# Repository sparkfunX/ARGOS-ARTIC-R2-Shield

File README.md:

# ARGOS Satellite Transceiver Shield

The [ARGOS ARTIC R2 satellite communication chipset](https://www.cls-telemetry.com/argos-solutions/argos-products/modems/artic-chipset/#1534863095666-398318f3-c367) in Thing Plus format.

[*SparkX ARGOS Satellite Transceiver Shield (SPX-17236)*](https://www.sparkfun.com/products/17236)

_Dimensions are in inches_  

The ARTIC-R2 is an integrated low power small size ARGOS 2/3/4 single chip radio. ARTIC-R2 implements a message based wireless interface. For satellite uplink communication, ARTIC-R2 will encode, modulate and transmit provided user messages. For downlink communication, ARTIC-R2 will lock to the downstream, demodulate and decode it and extract the satellite messages.

The ARTIC-R2 can transmit signals in frequency bands around 400MHz and receive signals in the bands around 466MHz, in accordance with the ARGOS satellite system specifications. The ARTIC-R2 is compliant to all ARGOS 3 and ARGOS 4 RX and TX standards. It contains a RF transceiver and frequency synthesizer and a digital baseband modem. The ARTIC-R2 contains an on-chip power amplifier delivering 1mW [0dBm] output power, that serves as an output for connecting an external high efficient PA. The (de)modulation algorithms run on an on-chip DSP. This software approach allows for retargeting the ARTIC for other applications. The DSP program can be retained on an external flash or the MCU.

- Serial interface (SPI) for communication with MCU
- Programmable DSP core on board to ensure flexibility
- RX frequency : 466MHz – TX frequency: 400MHz
- Fractional N frequency synthesis
- Supported TX standards:
  - BPSK: PTT-A2 (ARGOS 2), PTT-VLD (ARGOS 4)
  - QPSK: PTT-A3, PTT-ZE (ARGOS 3)
  - GMSK: PTT-HD (ARGOS 3), PTT-MD (ARGOS 4), PTT-HD (ARGOS 4)
- Supported RX standards:
  - BPSK: PMT-A3 (ARGOS 3)
  - DSSS OQPSK: PMT-A4 (ARGOS 4) not available
- Dedicated flash Interface to retain Firmware
- Support COSPAS-SARSAT standard
- Operates on external 26MHz reference clock
- Dual supply, 1.8V and 3.3V
- Integrated PA (0dBm) to combine with external PA

An RFPA0133 programmable gain power amplifier boosts the 0dBm (1mW) output from the ARTIC by up to 26dB, producing a maximum transmit power level of 400mW. The transmit power can be adjusted via the **G8** breakout pin.

The ARGOS satellite system is **currently** restricted to specific programs and applications. Please check that your project meets these requirements before buying hardware. [CLS (France)](https://www.cls-telemetry.com/argos-solutions/) and the [Woods Hole Group (America)](https://www.clsamerica.com/science-with-argos) will be able to advise if your project meets the requirements.
- _**"To meet system use requirements, all programs using Argos have to be related in some way or other to environmental protection, awareness or study, or to protecting human life."**_

## Repository Contents

- [**/Documents**](./Documents) - Datasheets, test certificates etc.
- [**/Hardware**](./Hardware) - Eagle PCB, SCH and LBR design files
- [**LICENSE.md**](./LICENSE,md) - contains the licence information

## Documentation

- [**Arduino Library**](https://github.com/sparkfun/SparkFun_ARGOS_ARTIC_R2_Arduino_Library) - SparkFun ARGOS ARTIC R2 Arduino Library
- [**Hookup Guide**](https://learn.sparkfun.com/tutorials/argos-artic-r2-satellite-transceiver-shield-hookup-guide) - a hookup guide for the SparkFun ARGOS Satellite Transceiver Shield - ARTIC R2

## Thanks

The SparkX ARGOS Satellite Transceiver Shield is a remix of the reference design kindly provided by the Arribada Initiative and Icoteq Ltd.

## License Information

This product is _**open source**_! 

Please review the LICENSE.md file for license information. 

If you have any questions or concerns on licensing, please contact technical support on our [SparkFun forums](https://forum.sparkfun.com/viewforum.php?f=152).

Distributed as-is; no warranty is given.

- Your friends at SparkFun.

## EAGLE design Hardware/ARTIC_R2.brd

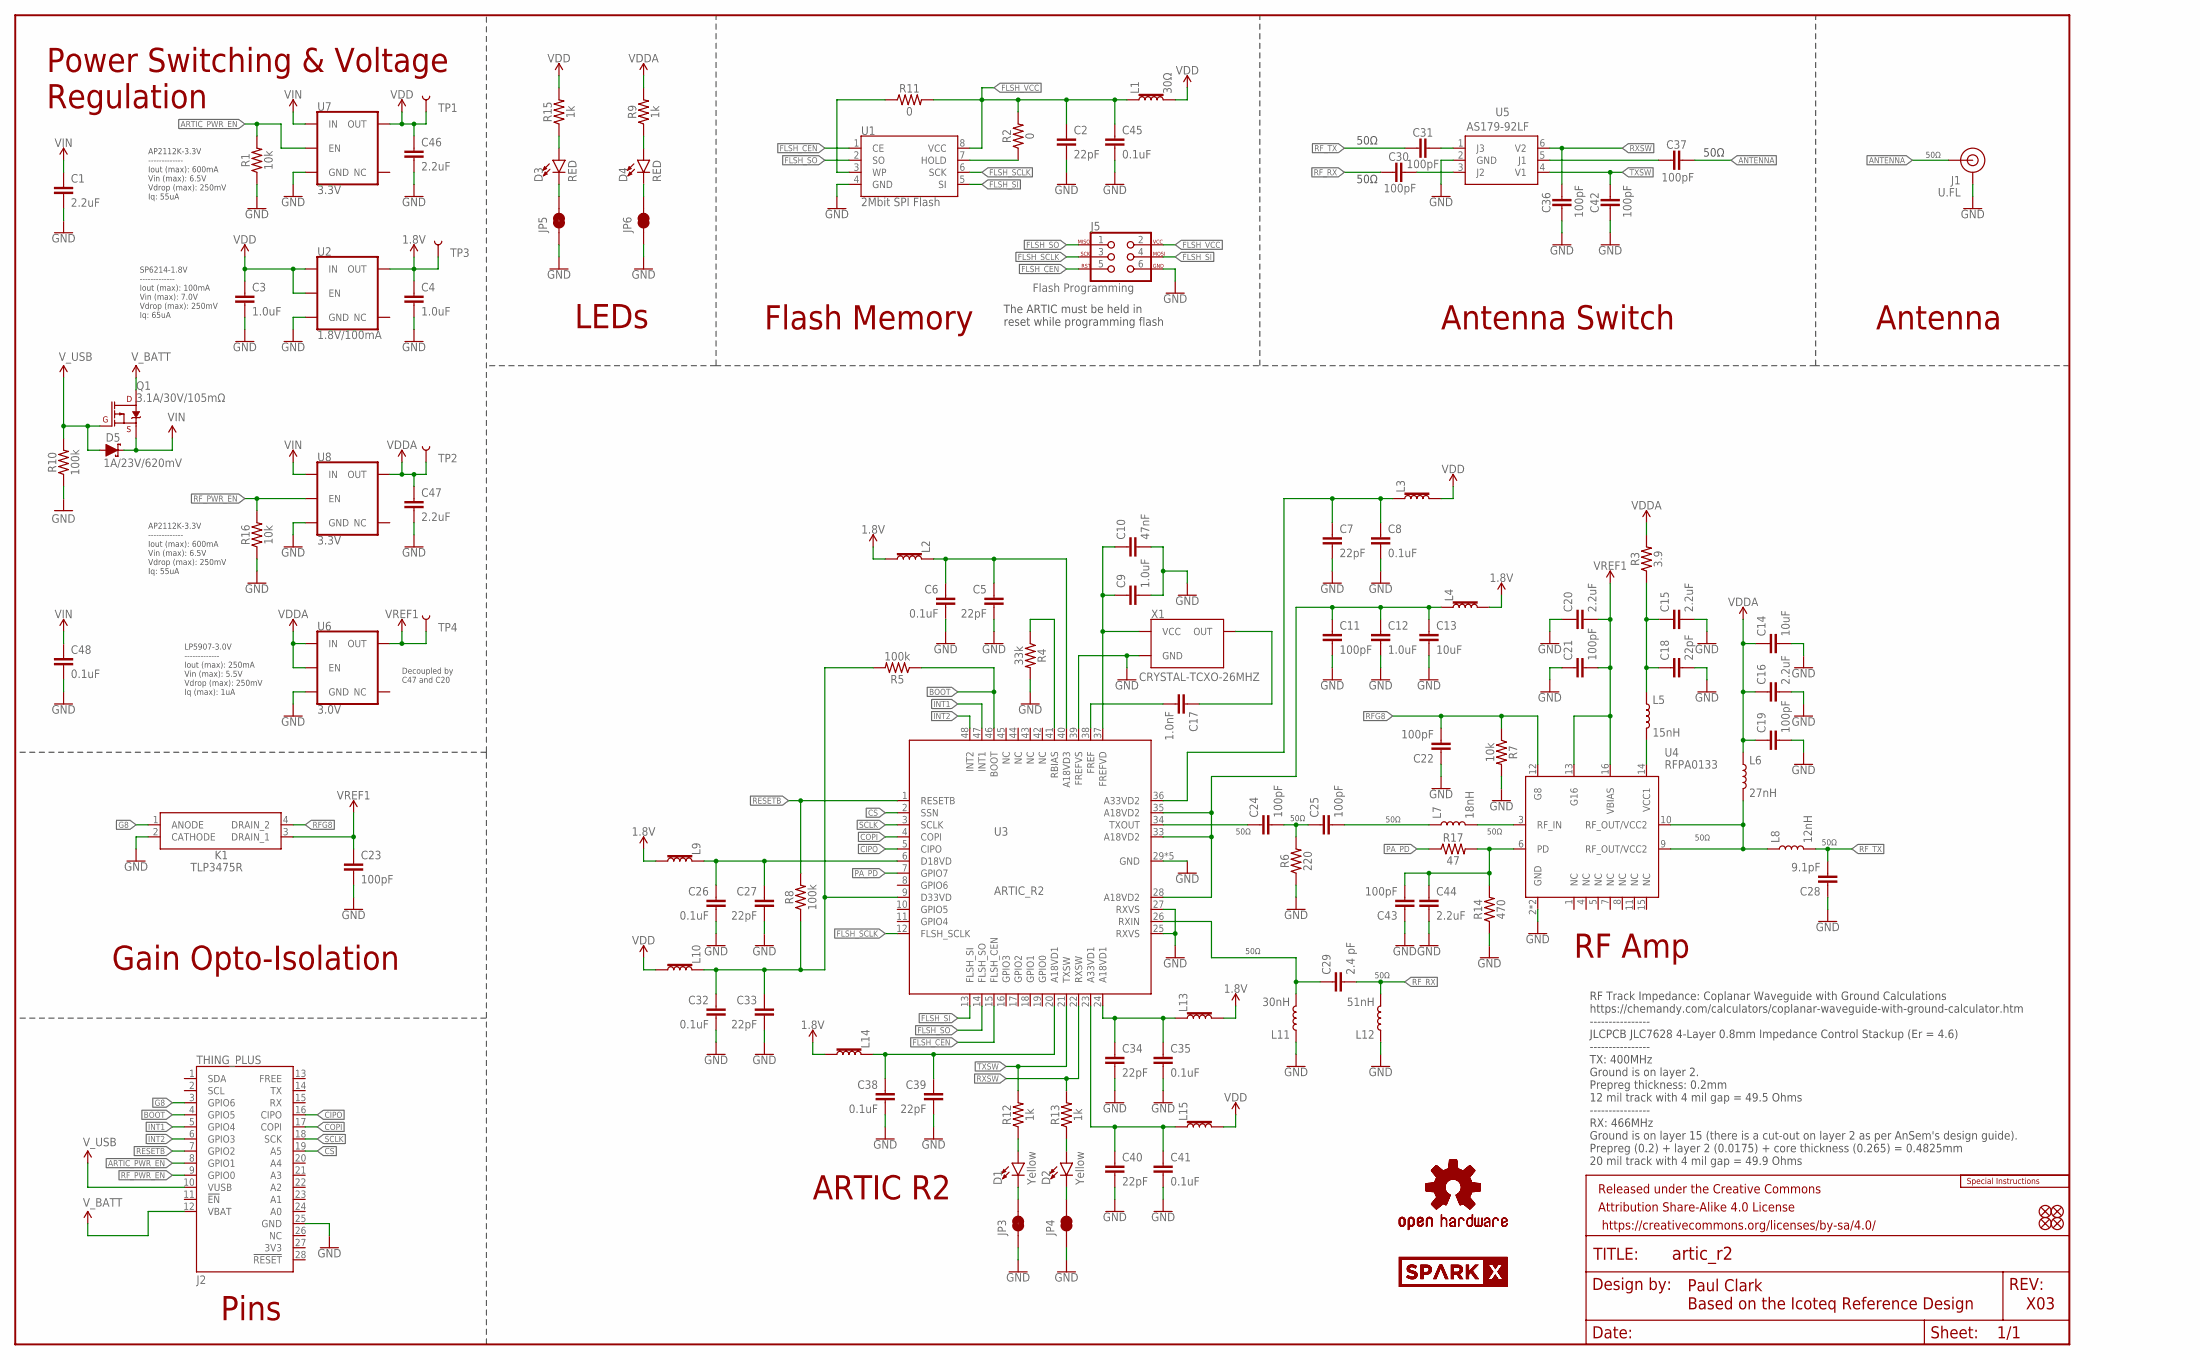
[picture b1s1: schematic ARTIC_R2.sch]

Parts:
C1, C15, C16, C20, C44, C46, C47: 2.2uF; 0402-TIGHT
C2, C5, C7, C18, C27, C33, C34, C39, C40: 22pF; 0402-TIGHT
C3, C4, C9, C12: 1.0uF; 0402-TIGHT
C6, C8, C26, C32, C35, C38, C41, C45, C48: 0.1uF; 0402-TIGHT
C10: 47nF; 0402-TIGHT
C11, C19, C21, C22, C23, C24, C25, C30, C31, C36, C37, C42, C43: 100pF; 0402-TIGHT
C13, C14: 10uF; 0402-TIGHT
C17: 1.0nF; 0402-TIGHT
C28: 9.1pF; 0402-TIGHT
C29: 2.4 pF; 0402_MURATA
D1, D2: Yellow; LED-0603
D3, D4: RED; LED-0603
D5: 1A/23V/620mV; SOD-323
FD1, FD2, FD3, FD4: FIDUCIAL1X2; FIDUCIAL-1X2
FRAME1: FRAME-LEDGER; CREATIVE_COMMONS
J1: U.FL
J2: THING_PLUS
J5: Flash Programming; 2X3_TEST_POINTS
JP3, JP4, JP5, JP6: JUMPER-SMT_2_NC_TRACE_SILK; SMT-JUMPER_2_NC_TRACE_SILK
K1: TLP3475R; TLP3475RTPF
L1, L2, L3, L4, L9, L10, L13, L14, L15: 30Ω; 0402-TIGHT
L5: 15nH; 0402_COILCRAFT
L6: 27nH; 0402_COILCRAFT
L7: 18nH; 0402_COILCRAFT
L8: 12nH; 0402_COILCRAFT
L11: 30nH; 0402_COILCRAFT
L12: 51nH; 0402_COILCRAFT
LOGO1: SPECIAL_INSTRUCTIONS-ORDERING; ORDERING_INSTRUCTIONS
LOGO2, LOGO3: OSHW-LOGOS; OSHW-LOGO-S
Q1: 3.1A/30V/105mΩ; SOT23-3
R1, R7, R16: 10k; 0402-TIGHT
R2, R11: 0; 0402-TIGHT
R3: 3.9; 0402-TIGHT
R4: 33k; 0402-TIGHT
R5, R8, R10: 100k; 0402-TIGHT
R6: 220; 0402-TIGHT
R9, R12, R13, R15: 1k; 0402-TIGHT
R14: 470; 0402-TIGHT
R17: 47; 0402-TIGHT
SPARKX1, SPARKX2: SPARKX-LOGO4; SPARKX-MEDIUM
TP1, TP2, TP3, TP4: TEST-POINTTP_15TH_THRU; TP_15TH
U1: 2Mbit SPI Flash; SO08
U2: 1.8V/100mA; SC70
U3: ARTIC_R2; QFN-48
U4: RFPA0133; QFN50P300X300X86-17N
U5: AS179-92LF; SOT65P220X100-6N
U6: 3.0V; SOT23-5
U7, U8: 3.3V; SOT23-5
X1: CRYSTAL-TCXO-26MHZ; CRYSTAL-TCXO-SMD-1.65X1.25

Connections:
1.8V: C4.1, L2.2, L4.2, L9.2, L13.2, L14.2, TP3.P$1, U2.5 (OUT)
ANTENNA: C37.1, J1.FEED (SIGNAL)
ARTIC_PWR_EN: J2.8 (GPIO1), R1.2, U7.3 (EN)
BOOT: J2.4 (GPIO5), R5.1, U3.46 (BOOT)
CIPO: J2.16 (CIPO), U3.5 (CIPO)
COPI: J2.17 (COPI), U3.4 (COPI)
CS: J2.19 (A5), U3.2 (SSN)
FLSH_CEN: J5.5, U1.1 (CE), U3.15 (FLSH_CEN)
FLSH_SCLK: J5.3, U1.6 (SCK), U3.12 (FLSH_SCLK)
FLSH_SI: J5.4, U1.5 (SI), U3.13 (FLSH_SI)
FLSH_SO: J5.1, U1.2 (SO), U3.14 (FLSH_SO)
FLSH_VCC: C2.1, C45.1, J5.2, L1.1, R2.2, R11.2, U1.8 (VCC)
G8: J2.3 (GPIO6), K1.1 (ANODE)
GND: C1.2, C2.2, C3.2, C4.2, C5.2, C6.2, C7.2, C8.2, C9.2, C10.2, C11.2, C12.2, C13.2, C14.2, C15.2, C16.2, C18.2, C19.2, C20.1, C21.1, C22.1, C23.2, C26.2, C27.2, C28.1, C32.2, C33.2, C34.2, C35.2, C36.2, C38.2, C39.2, C40.2, C41.2, C42.2, C43.1, C44.2, C45.2, C46.2, C47.2, C48.2, J1.1 (GND), J1.2 (GND), J2.25 (GND), J5.6, JP3.1, JP4.1, JP5.1, JP6.1, K1.2 (CATHODE), L11.P$1 (1), L12.P$1 (1), R1.1, R4.2, R6.1, R7.2, R10.1, R14.1, R16.1, U1.4 (GND), U2.2 (GND), U3.25 (RXVS), U3.27 (RXVS), U3.29 (GND), U3.30 (GND), U3.31 (GND), U3.32 (GND), U3.39 (FREFVS), U3.GND, U4.2 (GND), U4.EDAP (GND), U5.2 (GND), U6.2 (GND), U7.2 (GND), U8.2 (GND), X1.1 (GND), X1.2 (GND)
INT1: J2.5 (GPIO4), U3.47 (INT1)
INT2: J2.6 (GPIO3), U3.48 (INT2)
unnamed: R2.1, U1.7 (HOLD)
unnamed: R11.1, U1.3 (WP)
unnamed: C34.1, C35.1, L13.1, U3.24 (A18VD1)
unnamed: C40.1, C41.1, L15.1, U3.23 (A33VD1)
unnamed: D2.A, R13.1
unnamed: D1.A, R12.1
unnamed: C26.1, C27.1, L9.1, U3.6 (D18VD)
unnamed: C32.1, C33.1, L10.1, R5.2, R8.1, U3.9 (D33VD)
unnamed: C11.1, C12.1, C13.1, L4.1, U3.28 (A18VD2), U3.33 (A18VD2), U3.35 (A18VD2)
unnamed: C7.1, C8.1, L3.1, U3.36 (A33VD2)
unnamed: R4.1, U3.41 (RBIAS)
unnamed: C5.1, C6.1, L2.1, U3.40 (A18VD3)
unnamed: C9.1, C10.1, U3.37 (FREFVD), X1.4 (VCC)
unnamed: C17.1, X1.3 (OUT)
unnamed: C17.2, U3.38 (FREF)
unnamed: C24.1, U3.34 (TXOUT)
unnamed: C24.2, C25.1, R6.2
unnamed: L5.P$2 (2), U4.14 (VCC1)
unnamed: C15.1, C18.1, L5.P$1 (1), R3.1
unnamed: C29.P$1 (1), L11.P$2 (2), U3.26 (RXIN)
unnamed: D4.A, R9.1
unnamed: C25.2, L7.P$1 (1)
unnamed: L7.P$2 (2), U4.3 (RF_IN)
unnamed: L6.P$2 (2), L8.P$1 (1), U4.9 (RF_OUT/VCC2), U4.10 (RF_OUT/VCC2)
unnamed: D4.C, JP6.2
unnamed: C31.1, U5.1 (J3)
unnamed: C30.1, U5.3 (J2)
unnamed: C37.2, U5.5 (J1)
unnamed: C38.1, C39.1, L14.1, U3.20 (A18VD1)
unnamed: D1.C, JP3.2
unnamed: D2.C, JP4.2
unnamed: D3.A, R15.1
unnamed: D3.C, JP5.2
PA_PD: R17.1, U3.7 (GPIO7)
PD: C43.2, C44.1, R14.2, R17.2, U4.6 (PD)
RESETB: J2.7 (GPIO2), R8.2, U3.1 (RESETB)
RFG8: C22.2, K1.4 (DRAIN_2), R7.1, U4.12 (G8)
RF_PWR_EN: J2.9 (GPIO0), R16.2, U8.3 (EN)
RF_RX: C29.P$2 (2), C30.2, L12.P$2 (2)
RF_TX: C28.2, C31.2, L8.P$2 (2)
RXSW: C36.1, R13.2, U3.22 (RXSW), U5.6 (V2)
SCLK: J2.18 (SCK), U3.3 (SCLK)
TXSW: C42.1, R12.2, U3.21 (TXSW), U5.4 (V1)
VDD: C3.1, C46.1, L1.2, L3.2, L10.2, L15.2, R15.2, TP1.P$1, U2.1 (IN), U2.3 (EN), U7.5 (OUT)
VDDA: C14.1, C16.1, C19.1, C47.1, L6.P$1 (1), R3.2, R9.2, TP2.P$1, U6.1 (IN), U6.3 (EN), U8.5 (OUT)
VIN: C1.1, C48.1, D5.C, Q1.2 (S), U7.1 (IN), U8.1 (IN)
VREF1: C20.2, C21.2, C23.1, K1.3 (DRAIN_1), TP4.P$1, U4.13 (G16), U4.16 (VBIAS), U6.5 (OUT)
V_BATT: J2.12 (VBAT), Q1.3 (D)
V_USB: D5.A, J2.10 (VUSB), Q1.1 (G), R10.2

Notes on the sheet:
Paul Clark Based on the Icoteq Reference Design
X03
SP6214-1.8V ------------- Iout (max): 100mA Vin (max): 7.0V Vdrop (max): 250mV Iq: 65uA
Power Switching & Voltage Regulation
Flash Memory
Antenna Switch
Antenna
ARTIC R2
RF Amp
Pins
50Ω
LEDs
RF Track Impedance: Coplanar Waveguide with Ground Calculations https://chemandy.com/calculators/coplanar-waveguide-with-ground-calculator.htm ---------------- JLCPCB JLC7628 4-Layer 0.8mm Impedance Control Stackup (Er = 4.6) ---------------- TX: 400MHz Ground is on layer 2. Prepreg thickness: 0.2m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
Gain Opto-Isolation
The ARTIC must be held in reset while programming flash
AP2112K-3.3V ------------- Iout (max): 600mA Vin (max): 6.5V Vdrop (max): 250mV Iq: 55uA
LP5907-3.0V ------------- Iout (max): 250mA Vin (max): 5.5V Vdrop (max): 250mV Iq (max): 1uA
Decoupled by C47 and C20

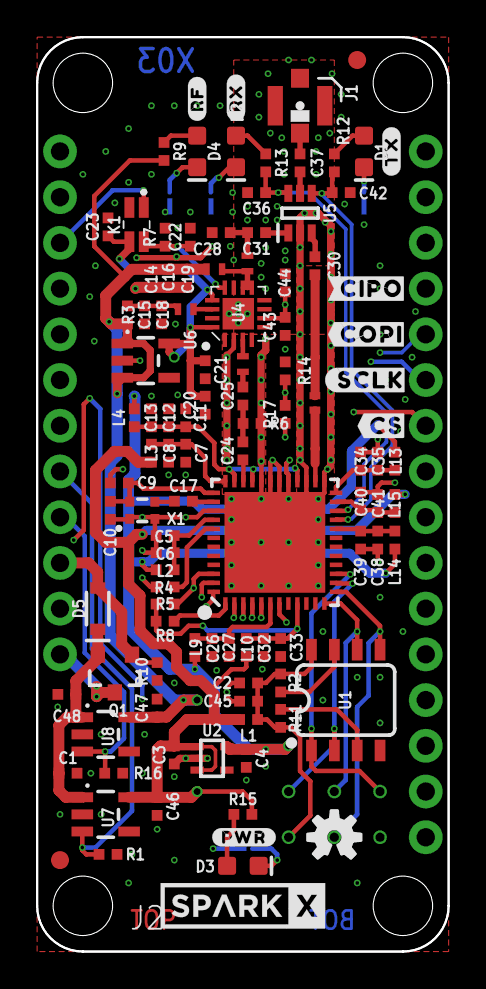
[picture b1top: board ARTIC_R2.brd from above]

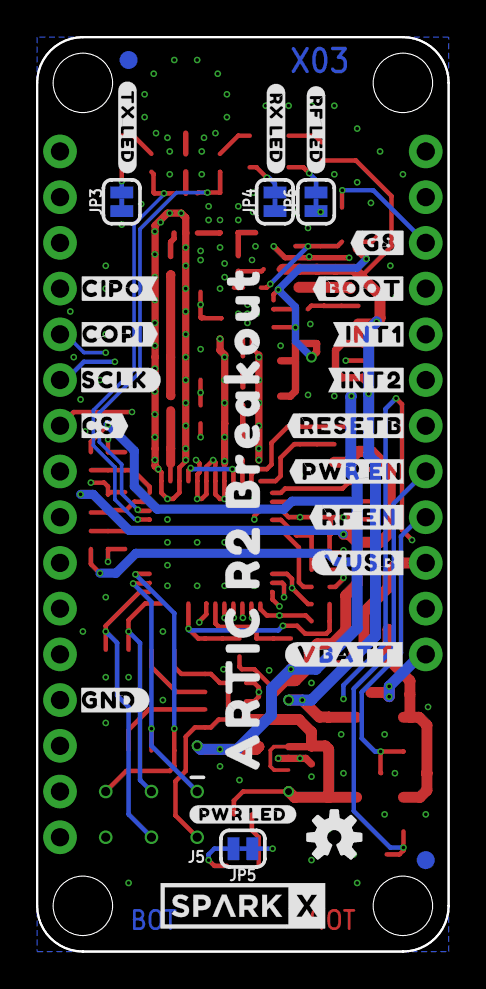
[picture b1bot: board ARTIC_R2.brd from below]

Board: 4 copper layers, 22.9 x 50.8 mm, 144 parts (28 on the bottom side), 65 nets.

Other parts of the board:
U$1: #TX#0
U$2: #RX#0
U$3: #RX_LED#0
U$4: #TX_LED#0
U$5: #RF_LED#0
U$6: #G8#0
U$7: #RF#0
U$8: #RF_EN#0
U$9: CIPO#0
U$10: #CIPO0
U$11: #COPI0
U$12: COPI#0
U$13: #SCLK0
U$14: SCLK#0
U$15: #CS0
U$16: CS#0
U$17: GND#0
U$18: #RESETB0
U$19: #PWR_EN0
U$20: #VBATT#0
U$21: #VUSB#0
U$24: #BOOT0
U$25: #INT10
U$26: #INT20
U$27: #PWR_LED#0
U$28: #PWR#0
U$29: ARTIC_R2_BREAKOUT0

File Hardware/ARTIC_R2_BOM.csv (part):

Part,Value,Device,Package,Description,DESCRIPTION,DESIGNER,DIGIKEY_PART,MANUFACTURER,MANUFACTURER_NAME,MANUFACTURER_PART_NUMBER,MANU_PART,MOUSER_PART,MOUSER_PART_NUMBER,MOUSER_PRICE-STOCK,PACKAGE,PROD_ID,REV,SF_ID,VALUE
C1,2.2uF,2.2UF-0402_TIGHT-10V-10%-X5R,0402-TIGHT,2.2µF ceramic capacitors,,,,,,,,,,,,CAP-14232,,,2.2uF
C2,22pF,22PF-0402T-16V-10%,0402-TIGHT,22pF ceramic capacitors,,,,,,,,,,,,CAP-14674,,,22pF
C3,1.0uF,1.0UF-0402T-16V-10%,0402-TIGHT,1µF ceramic capacitors,,,,,,,,,,,,CAP-12417,,,1.0uF
C4,1.0uF,1.0UF-0402T-16V-10%,0402-TIGHT,1µF ceramic capacitors,,,,,,,,,,,,CAP-12417,,,1.0uF
C5,22pF,22PF-0402T-16V-10%,0402-TIGHT,22pF ceramic capacitors,,,,,,,,,,,,CAP-14674,,,22pF
C6,0.1uF,0.1UF-0402T-6.3V-10%-X7R,0402-TIGHT,0.1µF ceramic capacitors,,,,,,,,,,,,CAP-14993,,,0.1uF
C7,22pF,22PF-0402T-16V-10%,0402-TIGHT,22pF ceramic capacitors,,,,,,,,,,,,CAP-14674,,,22pF
C8,0.1uF,0.1UF-0402T-6.3V-10%-X7R,0402-TIGHT,0.1µF ceramic capacitors,,,,,,,,,,,,CAP-14993,,,0.1uF
C9,1.0uF,1.0UF-0402T-16V-10%,0402-TIGHT,1µF ceramic capacitors,,,,,,,,,,,,CAP-12417,,,1.0uF
C10,47nF,47NF-0402_TIGHT-25V-10%-X7R,0402-TIGHT,47nF ceramic capacitors,,,,,,,,,,,,CAP-14243,,,47nF
C11,100pF,100PF-0402T-50V-5%,0402-TIGHT,100pF/0.1nF ceramic capacitors,,,,,,,,,,,,CAP-13458,,,100pF
C12,1.0uF,1.0UF-0402T-16V-10%,0402-TIGHT,1µF ceramic capacitors,,,,,,,,,,,,CAP-12417,,,1.0uF
C13,10uF,10UF-0402T-6.3V-20%,0402-TIGHT,10.0µF ceramic capacitors,,,,,,,,,,,,CAP-14848,,,10uF
C14,10uF,10UF-0402T-6.3V-20%,0402-TIGHT,10.0µF ceramic capacitors,,,,,,,,,,,,CAP-14848,,,10uF
C15,2.2uF,2.2UF-0402_TIGHT-10V-10%-X5R,0402-TIGHT,2.2µF ceramic capacitors,,,,,,,,,,,,CAP-14232,,,2.2uF
C16,2.2uF,2.2UF-0402_TIGHT-10V-10%-X5R,0402-TIGHT,2.2µF ceramic capacitors,,,,,,,,,,,,CAP-14232,,,2.2uF
C17,1.0nF,1.0NF/1000PF-0402_TIGHT-50V-10%,0402-TIGHT,"1nF/1,000pF ceramic capacitors",,,,,,,,,,,,CAP-14280,,,1.0nF
C18,22pF,22PF-0402T-16V-10%,0402-TIGHT,22pF ceramic capacitors,,,,,,,,,,,,CAP-14674,,,22pF
C19,100pF,100PF-0402T-50V-5%,0402-TIGHT,100pF/0.1nF ceramic capacitors,,,,,,,,,,,,CAP-13458,,,100pF
C20,2.2uF,2.2UF-0402_TIGHT-10V-10%-X5R,0402-TIGHT,2.2µF ceramic capacitors,,,,,,,,,,,,CAP-14232,,,2.2uF
C21,100pF,100PF-0402T-50V-5%,0402-TIGHT,100pF/0.1nF ceramic capacitors,,,,,,,,,,,,CAP-13458,,,100pF
C22,100pF,100PF-0402T-50V-5%,0402-TIGHT,100pF/0.1nF ceramic capacitors,,,,,,,,,,,,CAP-13458,,,100pF
C23,100pF,100PF-0402T-50V-5%,0402-TIGHT,100pF/0.1nF ceramic capacitors,,,,,,,,,,,,CAP-13458,,,100pF
C24,100pF,100PF-0402T-50V-5%,0402-TIGHT,100pF/0.1nF ceramic capacitors,,,,,,,,,,,,CAP-13458,,,100pF
C25,100pF,100PF-0402T-50V-5%,0402-TIGHT,100pF/0.1nF ceramic capacitors,,,,,,,,,,,,CAP-13458,,,100pF
C26,0.1uF,0.1UF-0402T-6.3V-10%-X7R,0402-TIGHT,0.1µF ceramic capacitors,,,,,,,,,,,,CAP-14993,,,0.1uF
C27,22pF,22PF-0402T-16V-10%,0402-TIGHT,22pF ceramic capacitors,,,,,,,,,,,,CAP-14674,,,22pF
C28,9.1pF,9.1PF-0402-TIGHT,0402-TIGHT,9.1pF ceramic capacitors,,,,,,,,609-500R07S9R1CV4T,,,,CAP-15278,,,9.1pF
C29,2.4 pF,2.4PF-0402,0402_MURATA,,,,,,,,,,,,,CAP-14351,,,2.4 pF
C30,100pF,100PF-0402T-50V-5%,0402-TIGHT,100pF/0.1nF ceramic capacitors,,,,,,,,,,,,CAP-13458,,,100pF
C31,100pF,100PF-0402T-50V-5%,0402-TIGHT,100pF/0.1nF ceramic capacitors,,,,,,,,,,,,CAP-13458,,,100pF
C32,0.1uF,0.1UF-0402T-6.3V-10%-X7R,0402-TIGHT,0.1µF ceramic capacitors,,,,,,,,,,,,CAP-14993,,,0.1uF
C33,22pF,22PF-0402T-16V-10%,0402-TIGHT,22pF ceramic capacitors,,,,,,,,,,,,CAP-14674,,,22pF
C34,22pF,22PF-0402T-16V-10%,0402-TIGHT,22pF ceramic capacitors,,,,,,,,,,,,CAP-14674,,,22pF
C35,0.1uF,0.1UF-0402T-6.3V-10%-X7R,0402-TIGHT,0.1µF ceramic capacitors,,,,,,,,,,,,CAP-14993,,,0.1uF
C36,100pF,100PF-0402T-50V-5%,0402-TIGHT,100pF/0.1nF ceramic capacitors,,,,,,,,,,,,CAP-13458,,,100pF
C37,100pF,100PF-0402T-50V-5%,0402-TIGHT,100pF/0.1nF ceramic capacitors,,,,,,,,,,,,CAP-13458,,,100pF
C38,0.1uF,0.1UF-0402T-6.3V-10%-X7R,0402-TIGHT,0.1µF ceramic capacitors,,,,,,,,,,,,CAP-14993,,,0.1uF
C39,22pF,22PF-0402T-16V-10%,0402-TIGHT,22pF ceramic capacitors,,,,,,,,,,,,CAP-14674,,,22pF
C40,22pF,22PF-0402T-16V-10%,0402-TIGHT,22pF ceramic capacitors,,,,,,,,,,,,CAP-14674,,,22pF
C41,0.1uF,0.1UF-0402T-6.3V-10%-X7R,0402-TIGHT,0.1µF ceramic capacitors,,,,,,,,,,,,CAP-14993,,,0.1uF
C42,100pF,100PF-0402T-50V-5%,0402-TIGHT,100pF/0.1nF ceramic capacitors,,,,,,,,,,,,CAP-13458,,,100pF
C43,100pF,100PF-0402T-50V-5%,0402-TIGHT,100pF/0.1nF ceramic capacitors,,,,,,,,,,,,CAP-13458,,,100pF
C44,2.2uF,2.2UF-0402_TIGHT-10V-10%-X5R,0402-TIGHT,2.2µF ceramic capacitors,,,,,,,,,,,,CAP-14232,,,2.2uF
C45,0.1uF,0.1UF-0402T-6.3V-10%-X7R,0402-TIGHT,0.1µF ceramic capacitors,,,,,,,,,,,,CAP-14993,,,0.1uF
C46,2.2uF,2.2UF-0402_TIGHT-10V-10%-X5R,0402-TIGHT,2.2µF ceramic capacitors,,,,,,,,,,,,CAP-14232,,,2.2uF
C47,2.2uF,2.2UF-0402_TIGHT-10V-10%-X5R,0402-TIGHT,2.2µF ceramic capacitors,,,,,,,,,,,,CAP-14232,,,2.2uF
C48,0.1uF,0.1UF-0402T-10V-10%-X7R,0402-TIGHT,0.1µF ceramic capacitors,,,,,,,,,,,,CAP-15083,,,0.1uF
D1,Yellow,LED-YELLOW0603,LED-0603,Yellow SMD LED,,,,,,,,,,,,DIO-09003,,,Yellow
D2,Yellow,LED-YELLOW0603,LED-0603,Yellow SMD LED,,,,,,,,,,,,DIO-09003,,,Yellow
D3,RED,LED-RED0603,LED-0603,Red SMD LED,,,,,,,,,,,,DIO-00819,,,RED
D4,RED,LED-RED0603,LED-0603,Red SMD LED,,,,,,,,,,,,DIO-00819,,,RED
D5,1A/23V/620mV,DIODE-SCHOTTKY-BAT20J,SOD-323,Schottky diode,,,,,,,,,,,,DIO-11623,,,1A/23V/620mV
J1,U.FL,U.FL2PIN,U.FL,SMD Antenna Connector - U.FL,,,,,,,,,,,,CONN-09193,,WRL-09144,U.FL
K1,TLP3475R,TLP3475R,TLP3475RTPF,Solid State Relays - PCB Mount Photo-IC 3mA 50V 5000Vrms,Solid State Relays - PCB Mount Photo-IC 3mA 50V 5000Vrms,,TLP3475R(TPFCT-ND - Cut Tape (CT),,Toshiba,TLP3475R,,,757-TLP3475RTPF,https://www.mouser.com/Search/Refine.aspx?Keyword=757-TLP3475RTPF,,IC-15447,,,
L1,30Ω,FERRITE_BEAD-0402-30OHM-100MHZ,0402-TIGHT,"Ferrite Bead (blocks, cores, rings, chokes, etc.)",,,,,,,,,,,,NDUC-15133,,,30Ω
L2,30Ω,FERRITE_BEAD-0402-30OHM-100MHZ,0402-TIGHT,"Ferrite Bead (blocks, cores, rings, chokes, etc.)",,,,,,,,,,,,NDUC-15133,,,30Ω
L3,30Ω,FERRITE_BEAD-0402-30OHM-100MHZ,0402-TIGHT,"Ferrite Bead (blocks, cores, rings, chokes, etc.)",,,,,,,,,,,,NDUC-15133,,,30Ω
L4,30Ω,FERRITE_BEAD-0402-30OHM-100MHZ,0402-TIGHT,"Ferrite Bead (blocks, cores, rings, chokes, etc.)",,,,,,,,,,,,NDUC-15133,,,30Ω
L5,15nH,15NH-0402,0402_COILCRAFT,,,,,,,,,994-0402HP-15NXGLU,,,,NDUC-15272,,,15nH
L6,27nH,27NH-0402,0402_COILCRAFT,,,,,,,,,994-0402HP-27NXGLU,,,,NDUC-15273,,,27nH
L7,18nH,18NH-0402,0402_COILCRAFT,,,,,,,,,994-0402HP-18NXGLU,,,,NDUC-15277,,,18nH
L8,12nH,12NH-0402,0402_COILCRAFT,,,,,,,,,994-0402HP-12NXGLU,,,,NDUC-15271,,,12nH
L9,30Ω,FERRITE_BEAD-0402-30OHM-100MHZ,0402-TIGHT,"Ferrite Bead (blocks, cores, rings, chokes, etc.)",,,,,,,,,,,,NDUC-15133,,,30Ω
L10,30Ω,FERRITE_BEAD-0402-30OHM-100MHZ,0402-TIGHT,"Ferrite Bead (blocks, cores, rings, chokes, etc.)",,,,,,,,,,,,NDUC-15133,,,30Ω
L11,30nH,30NH-0402,0402_COILCRAFT,,,,,,,,,994-0402HP-30NXGLU,,,,NDUC-15275,,,30nH
L12,51nH,51NH-0402,0402_COILCRAFT,,,,,,,,,994-0402HP-51NXGLU,,,,NDUC-15276,,,51nH
L13,30Ω,FERRITE_BEAD-0402-30OHM-100MHZ,0402-TIGHT,"Ferrite Bead (blocks, cores, rings, chokes, etc.)",,,,,,,,,,,,NDUC-15133,,,30Ω
L14,30Ω,FERRITE_BEAD-0402-30OHM-100MHZ,0402-TIGHT,"Ferrite Bead (blocks, cores, rings, chokes, etc.)",,,,,,,,,,,,NDUC-15133,,,30Ω
L15,30Ω,FERRITE_BEAD-0402-30OHM-100MHZ,0402-TIGHT,"Ferrite Bead (blocks, cores, rings, chokes, etc.)",,,,,,,,,,,,NDUC-15133,,,30Ω
Q1,3.1A/30V/105mΩ,MOSFET_PCH-DMG2307L,SOT23-3,P-channel MOSFETs,,,,,,,,,,,,TRANS-11308,,,3.1A/30V/105mΩ
R1,10k,10KOHM-0402T-1/16W-1%,0402-TIGHT,10kΩ resistor,,,,,,,,,,,,RES-14241,,,10k
R2,0,0OHM-0402T-1/10W,0402-TIGHT,0Ω resistor,,,,,,,,,,,,RES-14244,,,0
R3,3.9OHM,3.9OHM,0402-TIGHT,3.9Ω resistor,,,,,,,,603-RC0402FR-073R9L,,,,RES-15270,,,
R4,33k,33KOHM-0402T-1/16W-1%,0402-TIGHT,33kΩ resistor,,,,,,,,,,,,RES-15128,,,33k
R5,100k,100KOHM-0402T-1/16W-1%,0402-TIGHT,100kΩ resistor,,,,,,,,,,,,RES-13495,,,100k
R6,220OHM,220OHM,0402-TIGHT,220Ω resistor,,,,,,,,755-SFR01MZPF2200,,,,RES-15269,,,
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
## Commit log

2020-07-27 Work in progress
2020-07-27 Nearing completion
2020-07-27 Adjusted the RF track widths
2020-07-28 Added 4x4 test panel
2020-07-29 ).8mm PCB with Impedance Control
2020-09-15 Updated the flash memory
2020-09-15 PROD_ID updates
2020-09-15 Added the missing PROD_IDs
2020-10-15 X02 - just about complete
2020-10-16 Updates for X02
2020-10-16 Adding the PROD_ID for the Toshiba photorelay
2020-11-13 Adding the BOM
2020-11-15 Changing R7 from 10K to 1K
2020-11-19 Adding the board images
2020-11-19 Adding transparency
2020-11-24 Adding images to the hook up guide
2020-12-03 Updates for X03. Design now includes a 3.0V regulator for the RF amp gain and bias.
2020-12-03 Updating the ordering instructions
2020-12-07 Final tweaks for X03. Changed 8dB to G8. Increased annular ring to 3.5mil.
2020-12-07 Correcting the description of the G8 pin - for version X03 of the PCB
2020-12-08 Adding the missing PROD_IDs
2021-03-22 Adding our antenna datasheet
2021-03-22 Adding the test certificates
2021-03-22 Adding current draw
2021-03-26 Update product images
2021-04-20 Adding the certificate for ARGOS 3 (LDA3)
2021-11-22 Update README - add a link to the Hookup Guide

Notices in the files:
parts and their libraries:
SparkFun-Aesthetics: Licensing: Creative Commons ShareAlike 4.0 International - https://creativecommons.org/licenses/by-sa/4.0
SparkFun-Aesthetics: Released under the Creative Commons Attribution Share-Alike 4.0 License
SparkFun-Aesthetics: https://creativecommons.org/licenses/by-sa/4.0
